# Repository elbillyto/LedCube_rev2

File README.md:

# LedCube_rev2
4x4x4 Atmega 328P-based Led cube

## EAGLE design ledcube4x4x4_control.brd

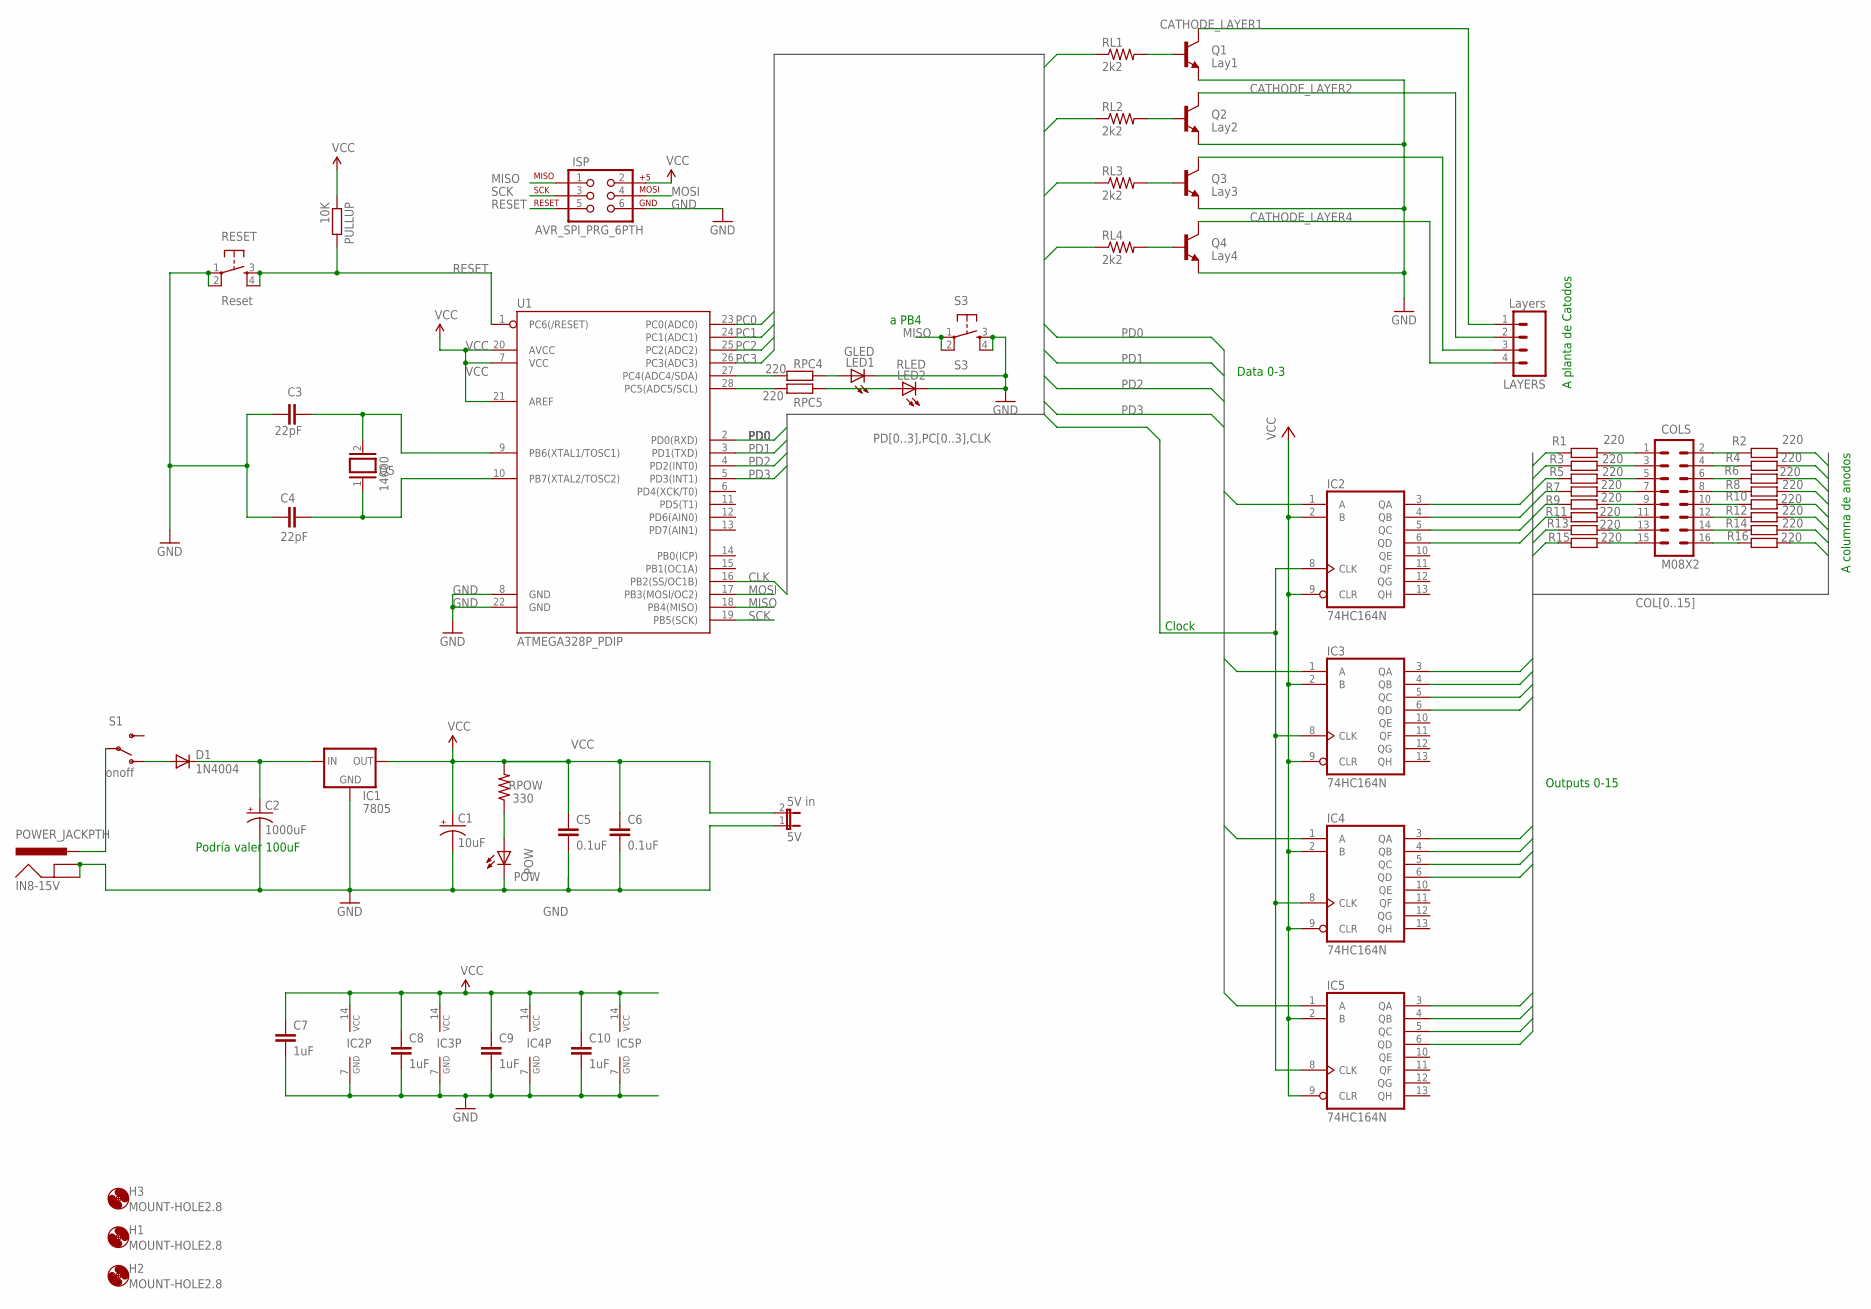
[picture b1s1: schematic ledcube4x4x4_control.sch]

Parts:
5V: 5V in; JP1; MPN 1-881545-1
C1: 10uF; CPOL-RADIAL-10UF-25V; MPN 100PK10MEFC5X11
C2: 1000uF; CPOL-RADIAL-1000UF-25V; MPN 35YXJ1000M12.5X20
C3, C4: 22pF; CAP-PTH-SMALLEZ
C5, C6: 0.1uF; CAP-PTH-SMALL-KIT
C7, C8, C9, C10: 1uF; CAP-PTH-SMALL-KIT
COLS: M08X2; 2X8
D1: 1N4004; DO41-10; MPN 1N4004-TP
H1, H2, H3: MOUNT-HOLE2.8; 2,8
IC1: 7805; TO220-IGO; MPN L7805ABV
IC2, IC3, IC4, IC5: 74HC164N; DIL14; MPN SN74HC164N
IN8-15V: POWER_JACKPTH; POWER_JACK_PTH
ISP: AVR_SPI_PRG_6PTH; 2X3
LAYERS: Layers; 1X04
LED1: GLED; LED5MM
LED2: RLED; LED5MM
POW: POW; LED3MM
PULLUP: 10K; 0207/10
Q1: Lay1; TO-92-AMMO
Q2: Lay2; TO-92-AMMO
Q3: Lay3; TO-92-AMMO
Q4: Lay4; TO-92-AMMO
Q5: 14000; QS
R1, R2, R3, R4, R5, R6, R7, R8, R9, R10, R11, R12, R13, R14, R15, R16: 220; 0207/10
RESET: Reset; TACTILE-PTH
RL1, RL2, RL3, RL4: 2k2; AXIAL-0.4
RPC4, RPC5: 220; 0207/10
RPOW: 330; AXIAL-0.4
S1: onoff; SWITCH-SPDT
S3: S3; TACTILE-PTH
U1: ATMEGA328P_PDIP; DIL28-3; MPN ATMEGA328P-PU

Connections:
BASE_LAYER1: Q1.2 (B), RL1.P$2 (2)
BASE_LAYER2: Q2.2 (B), RL2.P$2 (2)
BASE_LAYER3: Q3.2 (B), RL3.P$2 (2)
BASE_LAYER4: Q4.2 (B), RL4.P$2 (2)
CATHODE_LAYER1: LAYERS.1, Q1.3 (C)
CATHODE_LAYER2: LAYERS.2, Q2.3 (C)
CATHODE_LAYER4: LAYERS.4, Q4.3 (C)
CLK: IC2.8 (CLK), IC3.8 (CLK), IC4.8 (CLK), IC5.8 (CLK), U1.16 (PB2(SS/OC1B))
COL0: IC2.3 (QA), R1.1
COL1: IC2.4 (QB), R2.2
COL2: IC2.5 (QC), R3.1
COL3: IC2.6 (QD), R4.2
COL4: IC3.3 (QA), R5.1
COL5: IC3.4 (QB), R6.2
COL6: IC3.5 (QC), R7.1
COL7: IC3.6 (QD), R8.2
COL8: IC4.3 (QA), R9.1
COL9: IC4.4 (QB), R10.2
COL10: IC4.5 (QC), R11.1
COL11: IC4.6 (QD), R12.2
COL12: IC5.3 (QA), R13.1
COL13: IC5.4 (QB), R14.2
COL14: IC5.5 (QC), R15.1
COL15: IC5.6 (QD), R16.2
GND: 5V.1, C1.2 (-), C2.2 (-), C3.2, C4.2, C5.2, C6.2, C7.2, C8.2, C9.2, C10.2, IC1.GND, IC2.7 (GND), IC3.7 (GND), IC4.7 (GND), IC5.7 (GND), IN8-15V.GND, IN8-15V.GNDBREAK, ISP.6, LED1.K (C), LED2.K (C), POW.K (C), Q1.1 (E), Q2.1 (E), Q3.1 (E), Q4.1 (E), RESET.1, RESET.2, S3.3, S3.4, U1.8 (GND), U1.22 (GND)
MISO: ISP.1, S3.1, S3.2, U1.18 (PB4(MISO))
MOSI: ISP.4, U1.17 (PB3(MOSI/OC2))
unnamed: IN8-15V.PWR, S1.2
unnamed: C2.1 (+), D1.C, IC1.IN
unnamed: LED2.A, RPC5.2
unnamed: LED1.A, RPC4.2
unnamed: RPC5.1, U1.28 (PC5(ADC5/SCL))
unnamed: RPC4.1, U1.27 (PC4(ADC4/SDA))
unnamed: COLS.1, R1.2
unnamed: COLS.3, R3.2
unnamed: LAYERS.3, Q3.3 (C)
unnamed: COLS.5, R5.2
unnamed: C3.1, Q5.2, U1.9 (PB6(XTAL1/TOSC1))
unnamed: C4.1, Q5.1, U1.10 (PB7(XTAL2/TOSC2))
unnamed: COLS.7, R7.2
unnamed: COLS.15, R15.2
unnamed: COLS.13, R13.2
unnamed: COLS.11, R11.2
unnamed: COLS.9, R9.2
unnamed: D1.A, S1.1 (O)
unnamed: POW.A, RPOW.P$1 (1)
unnamed: COLS.2, R2.1
unnamed: COLS.4, R4.1
unnamed: COLS.6, R6.1
unnamed: COLS.8, R8.1
unnamed: COLS.10, R10.1
unnamed: COLS.12, R12.1
unnamed: COLS.14, R14.1
unnamed: COLS.16, R16.1
PC0: RL1.P$1 (1), U1.23 (PC0(ADC0))
PC1: RL2.P$1 (1), U1.24 (PC1(ADC1))
PC2: RL3.P$1 (1), U1.25 (PC2(ADC2))
PC3: RL4.P$1 (1), U1.26 (PC3(ADC3))
PD0: IC2.1 (A), U1.2 (PD0(RXD))
PD1: IC3.1 (A), U1.3 (PD1(TXD))
PD2: IC4.1 (A), U1.4 (PD2(INT0))
PD3: IC5.1 (A), U1.5 (PD3(INT1))
RESET: ISP.5, PULLUP.2, RESET.3, RESET.4, U1.1 (PC6(/RESET))
SCK: ISP.3, U1.19 (PB5(SCK))
VCC: 5V.2, C1.1 (+), C5.1, C6.1, C7.1, C8.1, C9.1, C10.1, IC1.OUT, IC2.2 (B), IC2.9 (CLR), IC2.14 (VCC), IC3.2 (B), IC3.9 (CLR), IC3.14 (VCC), IC4.2 (B), IC4.9 (CLR), IC4.14 (VCC), IC5.2 (B), IC5.9 (CLR), IC5.14 (VCC), ISP.2, PULLUP.1, RPOW.P$2 (2), U1.7 (VCC), U1.20 (AVCC), U1.21 (AREF)

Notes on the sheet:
Podría valer 100uF
A columna de anodos
A planta de Catodos
a PB4
Data 0-3
Clock
Outputs 0-15

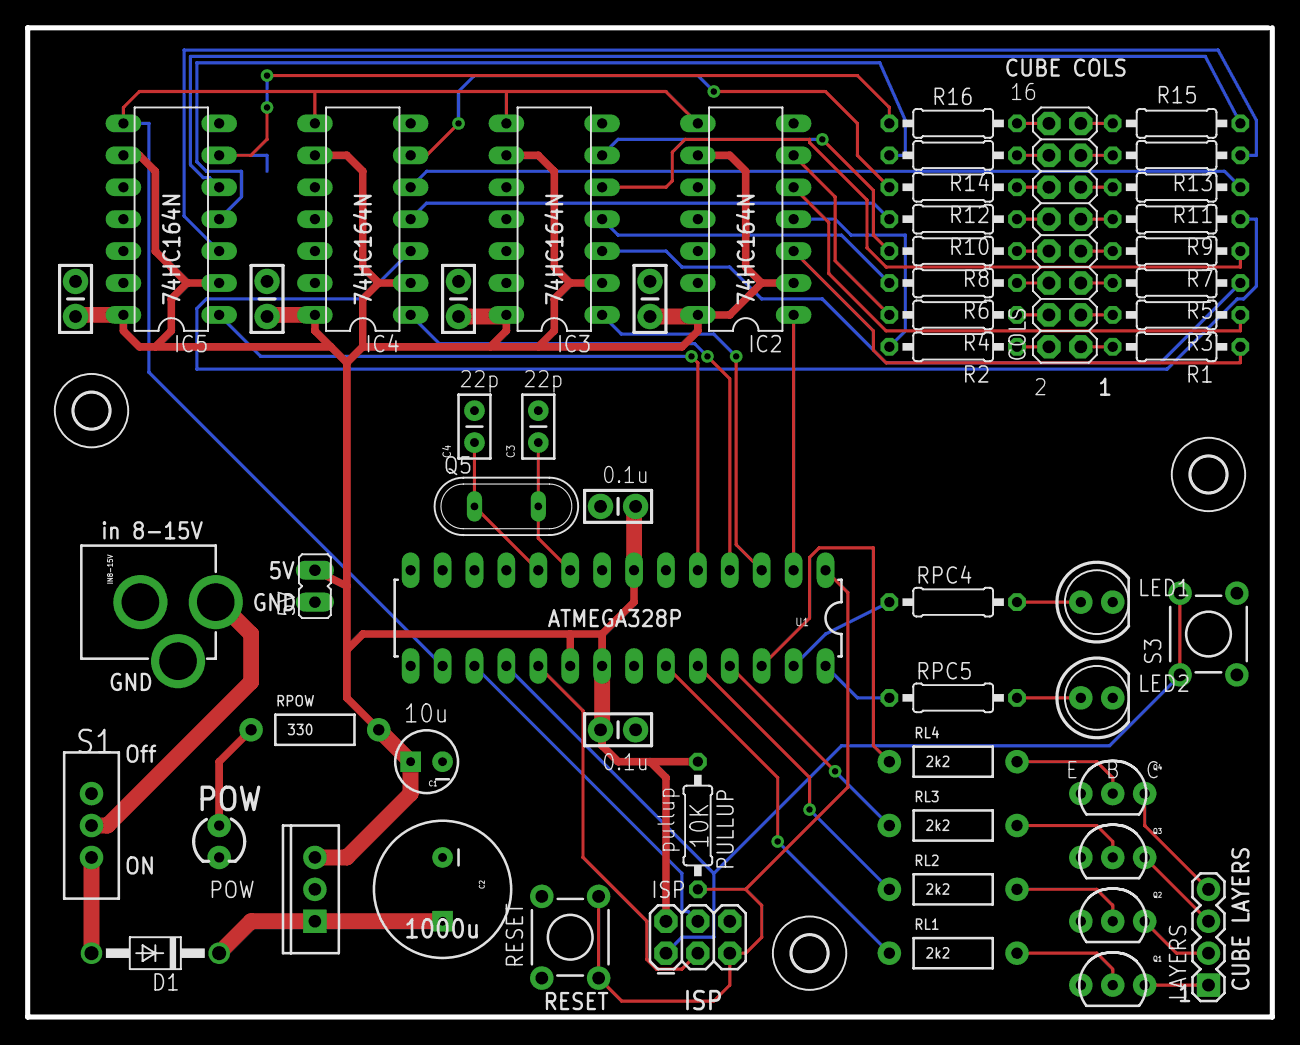
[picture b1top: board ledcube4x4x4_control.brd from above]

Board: 2 copper layers, 99.1 x 78.7 mm, 60 parts (0 on the bottom side), 65 nets.

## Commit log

2015-04-06 subida inicial
2015-04-07 firmware code not yet adapted to Atmega328P

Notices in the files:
parts and their libraries:
SparkFun-DigitalIC: Licensing: Creative Commons ShareAlike 4.0 International - https://creativecommons.org/licenses/by-sa/4.0
